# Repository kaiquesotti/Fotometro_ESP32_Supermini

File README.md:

# Fotometro_ESP32_Supermini

Documentação contendo projeto da PCB, código do arduino, código do aplicativo, aplicativo para android em .apk e arquivos stl do dispositivo. 

A montagem das peças dos arquivos tampa_cubeta e tampa deve ser feita usando um imã de 4x2 mm, a fim de serem conectadas de maneira facil.

As placas pcb foram feitas na china pela jlcbcb. Elas foram fixadas na base usando dupla face.

O projeto foi desenvolvido por Kaique de Sotti Silva e Flavio Camacho.

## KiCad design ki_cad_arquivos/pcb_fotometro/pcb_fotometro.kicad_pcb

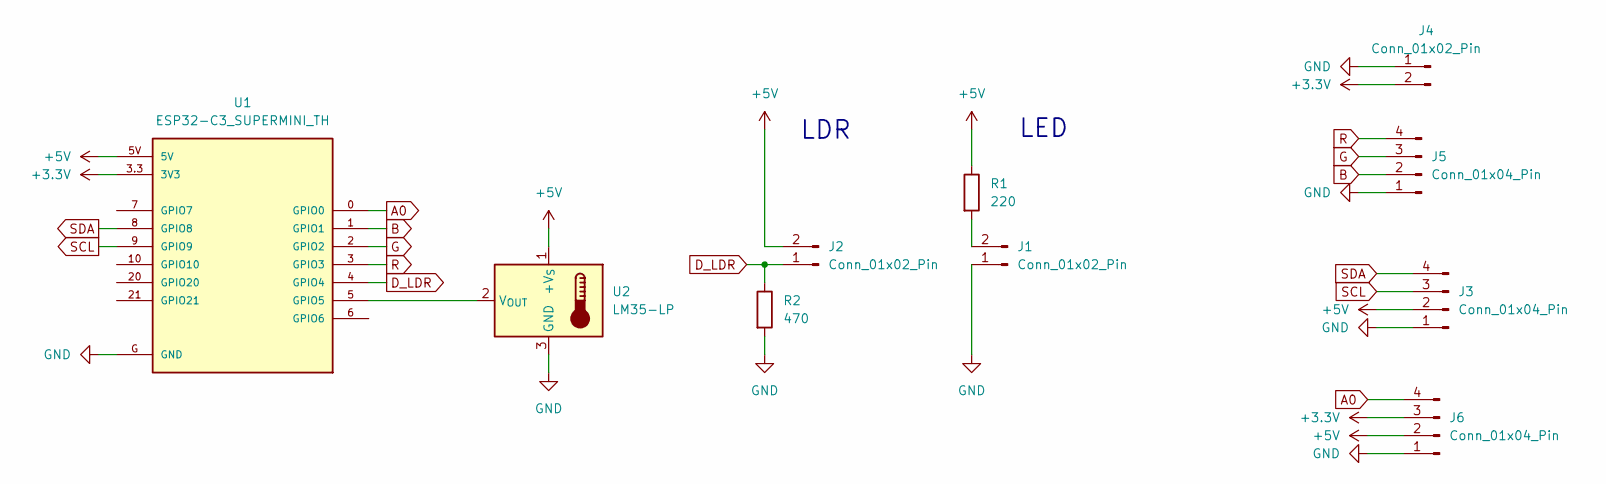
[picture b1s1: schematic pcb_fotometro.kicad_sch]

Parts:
J1, J2, J4: Conn_01x02_Pin; JST_XH_B2B-XH-A_1x02_P2.50mm_Vertical
J3, J5, J6: Conn_01x04_Pin; JST_XH_B4B-XH-A_1x04_P2.50mm_Vertical
R1: 220; R_Axial_DIN0207_L6.3mm_D2.5mm_P7.62mm_Horizontal
R2: 470; R_Axial_DIN0207_L6.3mm_D2.5mm_P7.62mm_Horizontal
U1: ESP32-C3_SUPERMINI_TH; MODULE_ESP32-C3_SUPERMINI_TH
U2: LM35-LP; TO-92_Inline_Horizontal1

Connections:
+3.3V: J4.2, J6.3, U1.3.3 (3V3)
+5V: J2.2, J3.2, J6.2, R1.1, U1.5V, U2.1 (+V_{S})
A0: J6.4, U1.0 (GPIO0)
B: J5.2, U1.1 (GPIO1)
D_LDR: J2.1, R2.1, U1.4 (GPIO4)
G: J5.3, U1.2 (GPIO2)
GND: J1.1, J3.1, J4.1, J5.1, J6.1, R2.2, U1.G (GND), U2.3 (GND)
unnamed: J1.2, R1.2
unnamed: U1.5 (GPIO5), U2.2 (V_{OUT})
R: J5.4, U1.3 (GPIO3)
SCL: J3.3, U1.9 (GPIO9)
SDA: J3.4, U1.8 (GPIO8)

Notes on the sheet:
LED
LDR

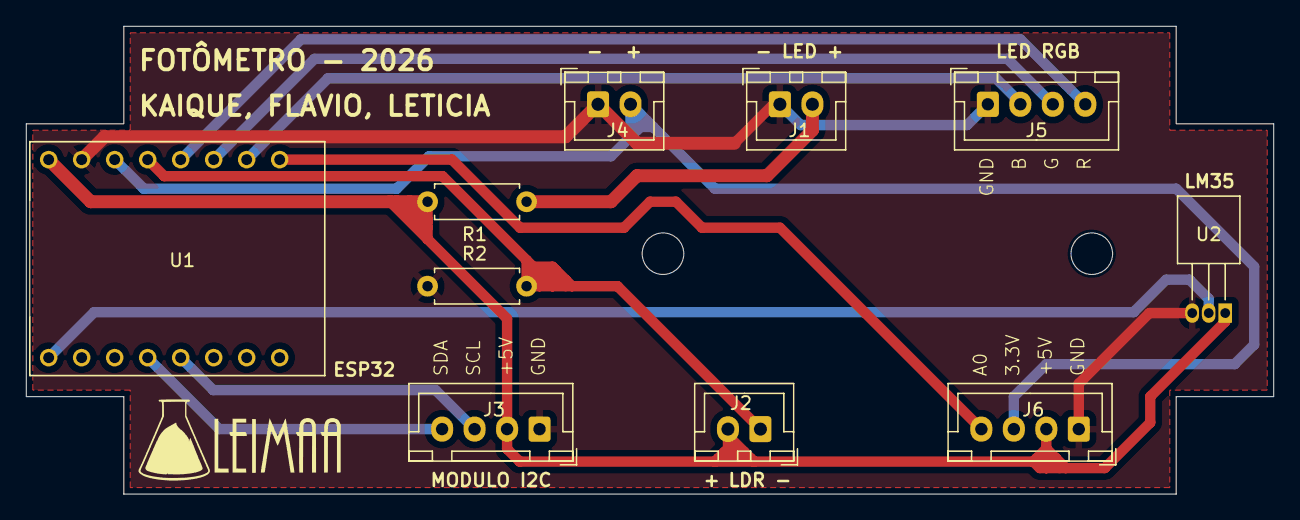
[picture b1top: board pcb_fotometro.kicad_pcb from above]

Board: 2 copper layers, 96.0 x 36.0 mm, 10 parts (0 on the bottom side), 12 nets.

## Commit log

2026-05-25 Create Codigo_esp32C3
